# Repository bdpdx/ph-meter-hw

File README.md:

# phMeter
## A simple combination pH probe interface circuit

This is a simple analog front end (AFE), ADC and I2C isolator circuit to interface to a standard combination pH electrode.

## Circuit Theory of Operation
### AFE
A standard combination pH probe has the following electrial characteristics
- Very high output impedance (100MOhm - 1GOhm)
- Bipolar sub 1V output voltage (+/- 400mV)

The first characteristic requires careful circuit design.  First we must convert that high output impedance to a much lower one for input into an ADC.  U2, a LMP7721 opamp does this for us.  Next the really high output impedance has issues with leakage current.  Because the current drawn from the sensor is in the 100s of pA range, any current lost to leakage will have a significant effect on the reading from the sensor.  To combat leakage current, guard rings around and below the high impedance traces are employed.  The LMP7721 is specifically designed for this using a special pinout that allows easy implementation of a guard ring.  As well as using low leakage tanalum capacitors for supply bypassing on the opamp.  The pA range currents also require careful selection of the opamp.  The TI LMP7721 choosen is used because of its fA range input bias currents.  Most opamps with pA or even uA input bias currents will completely destroy or at best significantly affect the probe readings.
The second characteristic isn't as much of an issue.  One could use an ADC that is bipolar (positive and negative supplied) and directly read the negative output voltage of the sensor.  However, generating the negative supply requires more circuitry and more importantly often times injects a large source of noise into the system.  Another approach, the one used here, is to bias (shift) the sensor output up enough so that the sensor output never swings negative.  U4 (another LMP7721) is used to bias the reference electrode up by +512mV.  Often the reference electrode is connected to GND, but by doing this the sensor will give an output of ~100mV-900mV.  The voltage required to bias the sensor is generated by U5, a MCP1501 1.024V reference voltage source.  The output of U5 is passed to a voltage divider to obtain 512mV.  Which leads to the ...
### ADC
Dividing the reference voltage using a resistor divider introduces error as well.  The tolerances and thermal coeffecients of the resistors will lead to error in this new "reference" voltage which is biased into the sensor output voltage.  To remove these errors, a differential ADC is used.  U1, a LTC2473, is a 16bit sigma-delta differential input ADC with I2C output.  For the LTC2473, a ~1kOhm input resistance is recommended as well as a 0.1uF input capacitor.  The LTC2473 has a internally generated reference voltage of 1.25V.  With an input voltage range from the sensor of 0.1V to 0.9V, most all of the range of the ADC is utilized.
### I2C Isolation
We want galvanic isolation between the sensor and the rest of the system. This reduces the noise injected into the system as well as this system interferring with any other (potential) systems measuring the same sample, or vice versa.  The ADM3260, U3, provides an isolated power supply, ground and I2C bus drivers for this application.  The resistor divider of R7 and R8 sets the output voltage of the isolated DC-DC converter, in this case the output voltage is set to 3.3V to match the input voltage.

## Performance
*COMING SOON*

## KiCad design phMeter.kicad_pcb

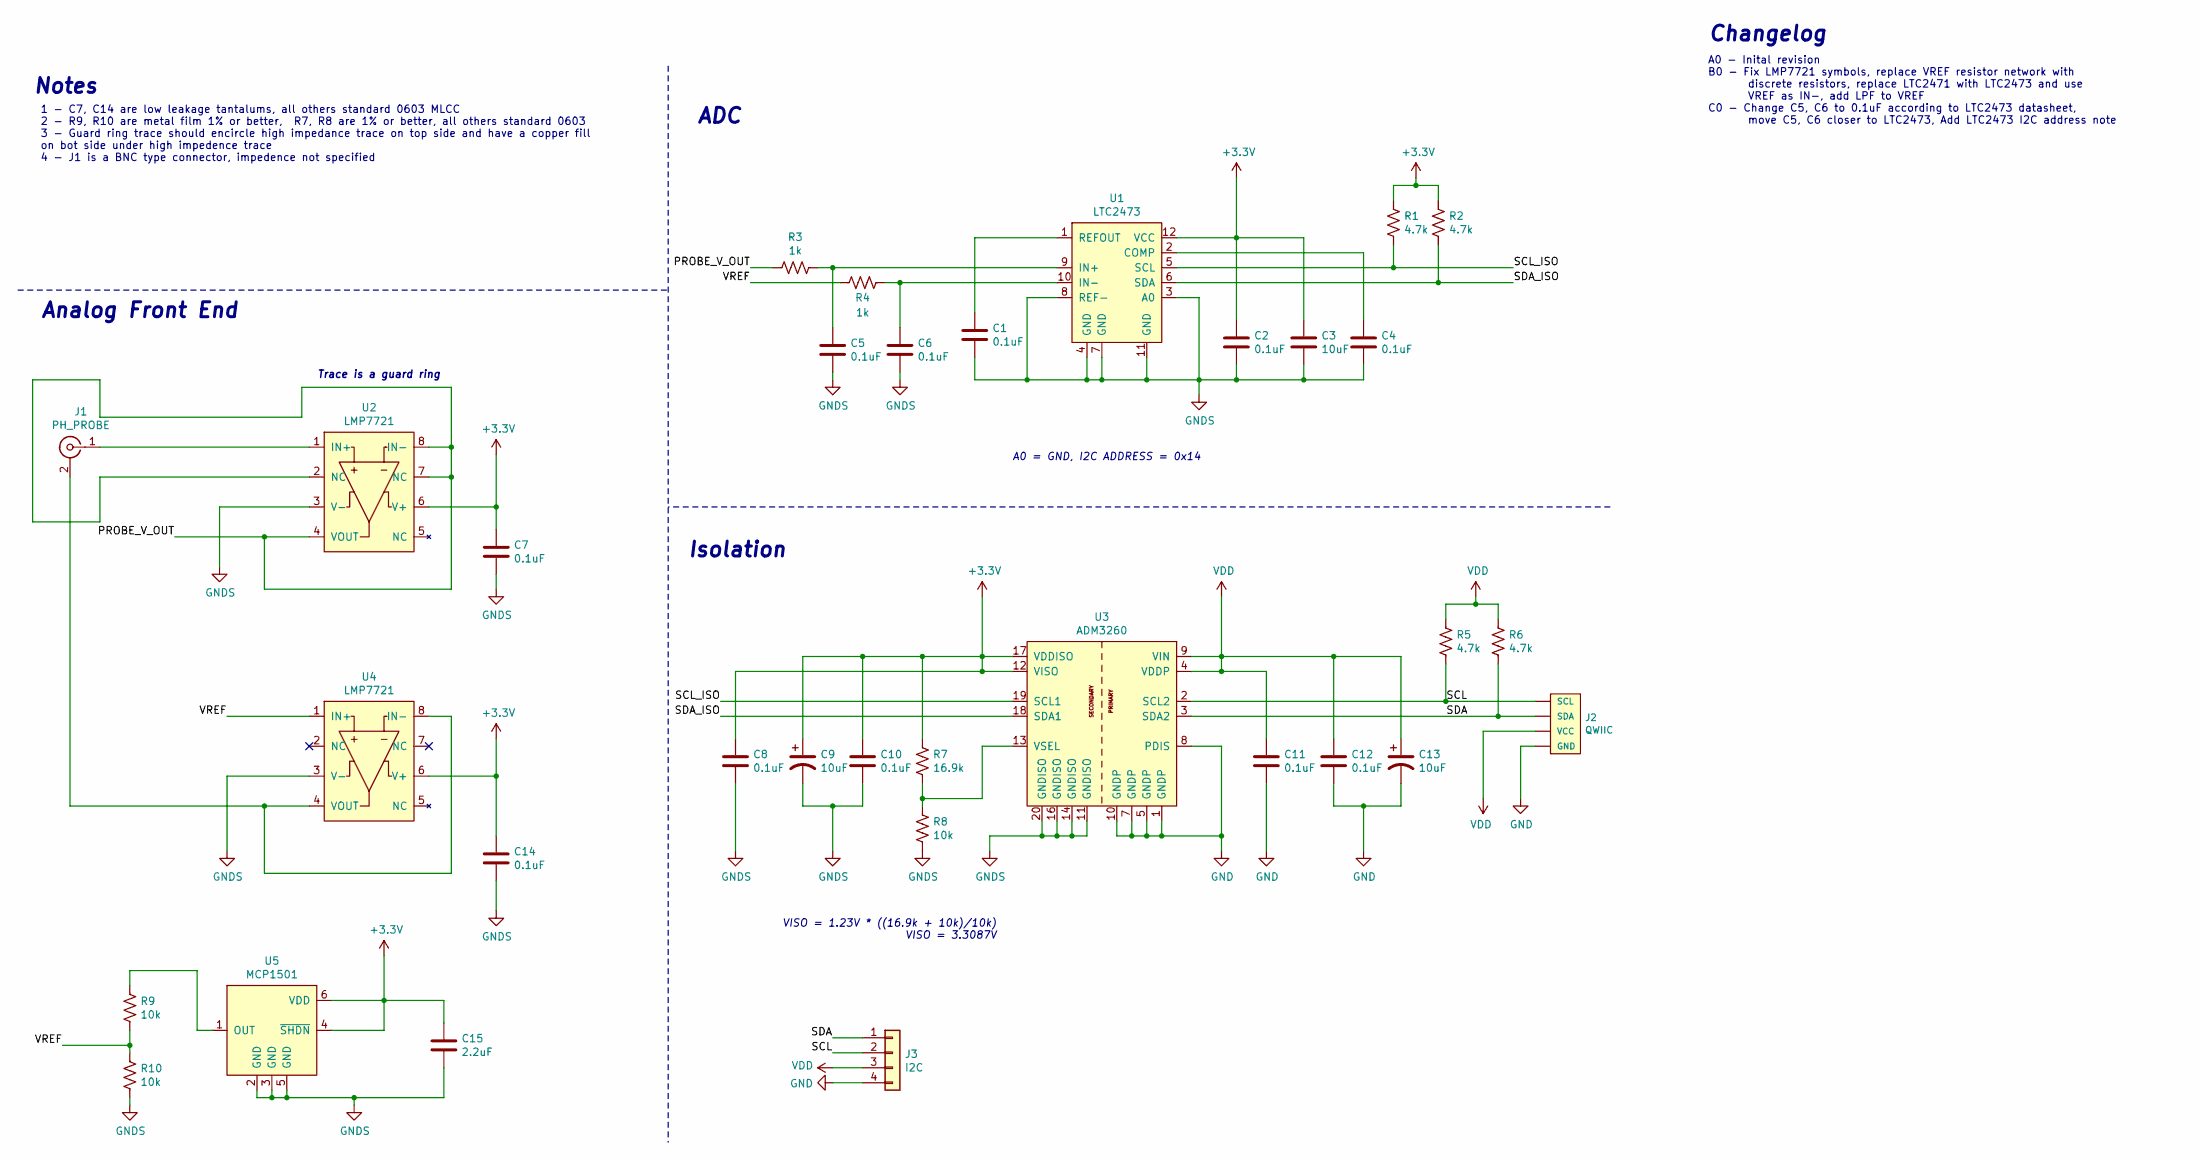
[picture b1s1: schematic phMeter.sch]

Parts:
C1, C2, C4, C5, C6, C8, C10, C11, C12: 0.1uF; C_0603_1608Metric; Digikey 311-1088-1-ND
C3, C9, C13: 10uF; C_0603_1608Metric; Digikey 445-9065-1-ND
C7, C14: 0.1uF; CP_EIA-2012-15_AVX-P; Digikey 478-11592-1-ND
C15: 2.2uF; C_0603_1608Metric; Digikey 445-6933-1-ND
J1: PH_PROBE; BNC_Amphenol_B6252HB-NPP3G-50_Horizontal; Digikey ARF2869-ND
J2: QWIIC; QWIIC_STEMMA_QT; Digikey 455-1804-1-ND
J3: I2C; PinHeader_1x04_P2.54mm_Horizontal; Digikey DNP
R1, R2, R5, R6: 4.7k; R_0603_1608Metric; Digikey RMCF0603FT4K70CT-ND
R3, R4: 1k; R_0603_1608Metric; Digikey P1.00KHCT-ND
R7: 16.9k; R_0603_1608Metric; Digikey P16.9KHCT-ND
R8: 10k; R_0603_1608Metric; Digikey P10.0KHCT-ND
R9, R10: 10k; R_0603_1608Metric; Digikey 2019-RN73H1JTTD1002F100CT-ND
U1: LTC2473; MSOP-12_3x4mm_P0.65mm; Digikey LTC2473CMS#PBF-ND
U2, U4: LMP7721; SOIC-8_3.9x4.9mm_P1.27mm; Digikey LMP7721MA/NOPB-ND
U3: ADM3260; SSOP-20_5.3x7.2mm_P0.65mm; Digikey ADM3260ARSZ-RL7CT-ND
U5: MCP1501; SOT-23-6; Digikey MCP1501T-10E/CHYCT-ND

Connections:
+3V3: C2.1, C3.1, C7.1, C8.1, C9.1, C10.1, C14.1, C15.1, R1.1, R2.1, R7.1, U1.12 (VCC), U2.6 (V+), U3.12 (VISO), U3.17 (VDDISO), U4.6 (V+), U5.4 (~SHDN), U5.6 (VDD)
/PROBE_V_OUT: R3.2, U2.2 (NC), U2.4 (VOUT), U2.7 (NC), U2.8 (IN-)
/SCL: J2.4 (SCL), J3.2, R5.2, U3.2 (SCL2)
/SCL_ISO: R1.2, U1.5 (SCL), U3.19 (SCL1)
/SDA: J2.3 (SDA), J3.1, R6.2, U3.3 (SDA2)
/SDA_ISO: R2.2, U1.6 (SDA), U3.18 (SDA1)
/VREF: R4.2, R9.2, R10.1, U4.1 (IN+)
GND: C11.2, C12.2, C13.2, J2.1 (GND), J3.4, U3.1 (GNDP), U3.5 (GNDP), U3.7 (GNDP), U3.8 (PDIS), U3.10 (GNDP)
GNDS: C1.2, C2.2, C3.2, C4.2, C5.2, C6.2, C7.2, C8.2, C9.2, C10.2, C14.2, C15.2, R8.2, R10.2, U1.3 (A0), U1.4 (GND), U1.7 (GND), U1.8 (REF-), U1.11 (GND), U2.3 (V-), U3.11 (GNDISO), U3.14 (GNDISO), U3.16 (GNDISO), U3.20 (GNDISO), U4.3 (V-), U5.2 (GND), U5.3 (GND), U5.5 (GND)
unnamed: C1.1, U1.1 (REFOUT)
unnamed: C4.1, U1.2 (COMP)
unnamed: C5.1, R3.1, U1.9 (IN+)
unnamed: C6.1, R4.1, U1.10 (IN-)
unnamed: J1.1 (In), U2.1 (IN+)
unnamed: J1.2 (Ext), U4.4 (VOUT), U4.8 (IN-)
unnamed: R7.2, R8.1, U3.13 (VSEL)
unnamed: R9.1, U5.1 (OUT)
VDD: C11.1, C12.1, C13.1, J2.2 (VCC), J3.3, R5.1, R6.1, U3.4 (VDDP), U3.9 (VIN)

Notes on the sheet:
Trace is a guard ring
VISO = 1.23V * ((16.9k + 10k)/10k) VISO = 3.3087V
Analog Front End
ADC
Isolation
Notes
1 - C7, C14 are low leakage tantalums, all others standard 0603 MLCC 2 - R9, R10 are metal film 1% or better, R7, R8 are 1% or better, all others standard 0603 3 - Guard ring trace should encircle high impedance trace on top side and have a copper fill on bot side under high impedence trace 4 - J1 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
A0 - Inital revision B0 - Fix LMP7721 symbols, replace VREF resistor network with discrete resistors, replace LTC2471 with LTC2473 and use VREF as IN-, add LPF to VREF C0 - Change C5, C6 to 0.1uF according to LTC2473 datasheet, move C5, C6 closer to LTC2473, Add LTC2473 I2C address note
Changelog
A0 = GND, I2C ADDRESS = 0x14

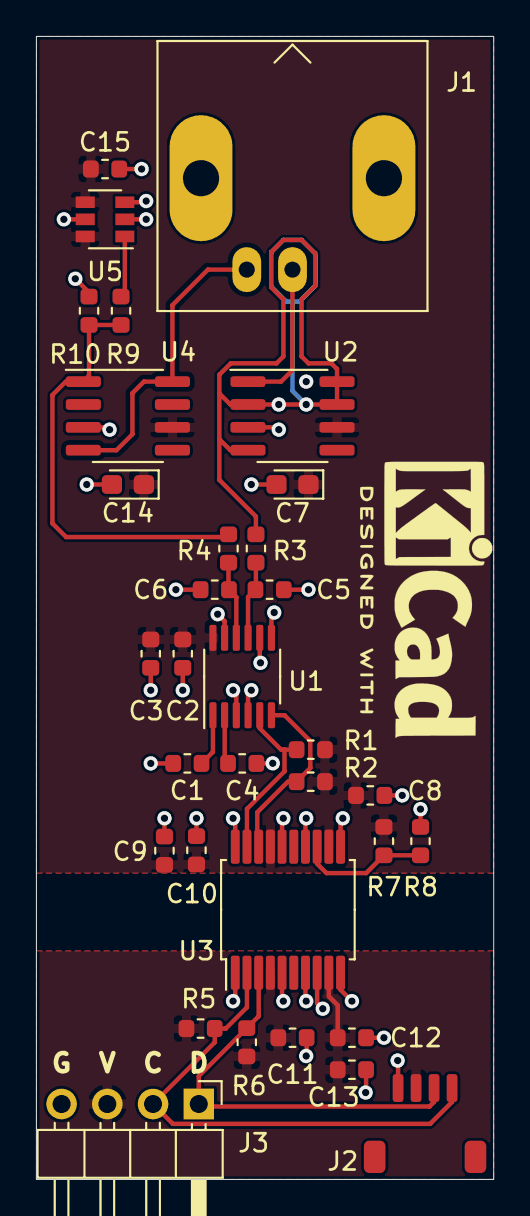
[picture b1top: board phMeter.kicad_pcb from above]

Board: 2 copper layers, 25.4 x 63.5 mm, 33 parts (0 on the bottom side), 18 nets.

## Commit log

2021-06-07 REV A0
2021-06-08 SCH REV B0, PCB REV B0
2021-06-09 SCH REV C0, PCB REV C0, added simulation files
2021-06-10 Add README and device datasheets
2021-06-10 Fix README
